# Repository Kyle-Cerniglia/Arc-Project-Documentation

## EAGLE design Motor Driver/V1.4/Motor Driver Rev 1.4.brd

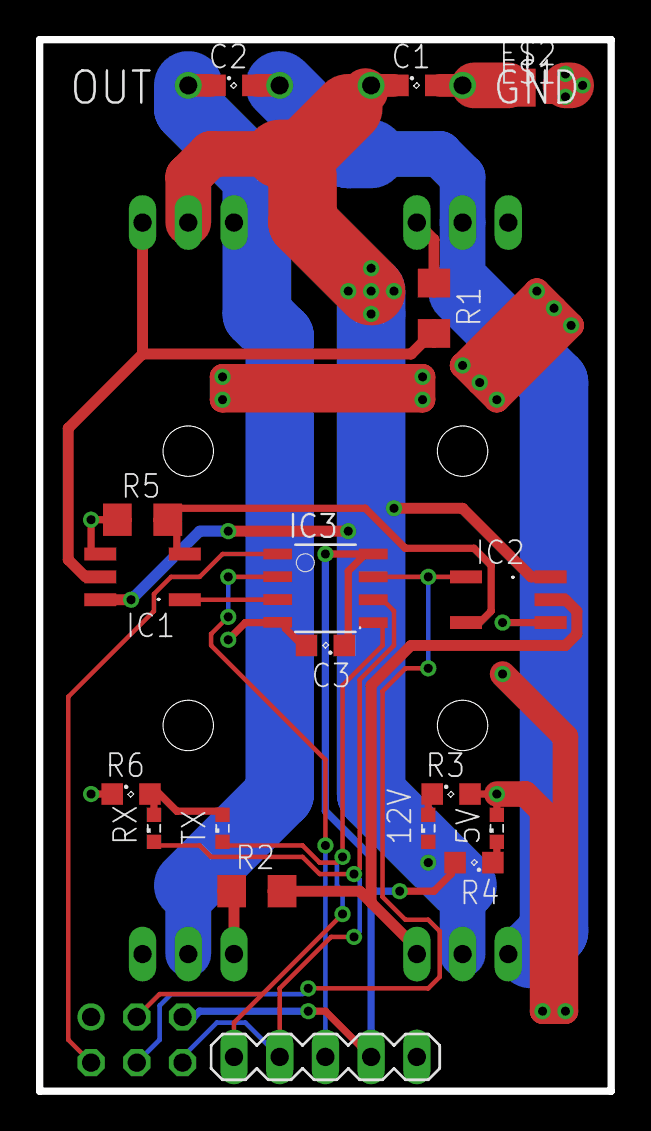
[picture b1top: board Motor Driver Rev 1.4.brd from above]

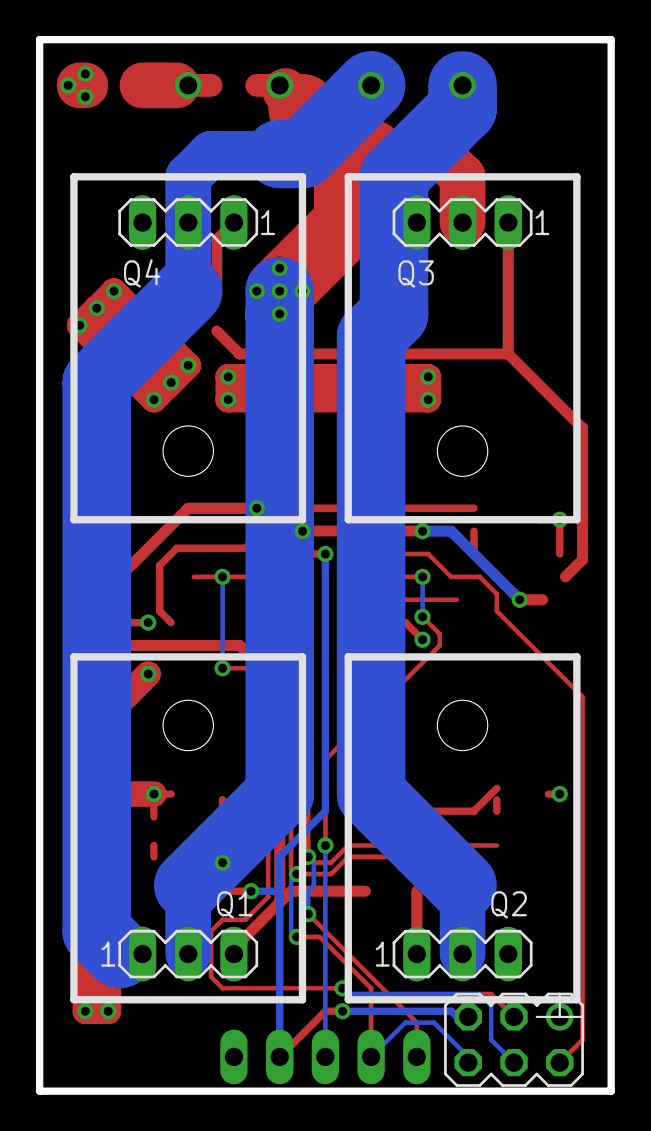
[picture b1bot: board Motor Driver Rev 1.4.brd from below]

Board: 2 copper layers, 31.8 x 58.4 mm, 24 parts (5 on the bottom side), 4 nets.

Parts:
5V, 12V: SML0603
C1, C2, C3: SML0805
E$1, E$2: POWERDI323
E$3: MA05-1
E$4: MA03-2
IC1, IC2: SOIC-6-5
IC3: 8S1
Q1, Q2, Q3, Q4: MA03-1
R1, R2, R5: PT1206
R3, R4, R6: SML0805
RX: SML0603
TX: SML0603

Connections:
GND: E$3.5, E$4.GND, Q2.GND, Q4.GND
S$28: E$3.2, E$4.6
S$33: E$3.4, E$4.5
S$37: E$3.GND, E$4.3

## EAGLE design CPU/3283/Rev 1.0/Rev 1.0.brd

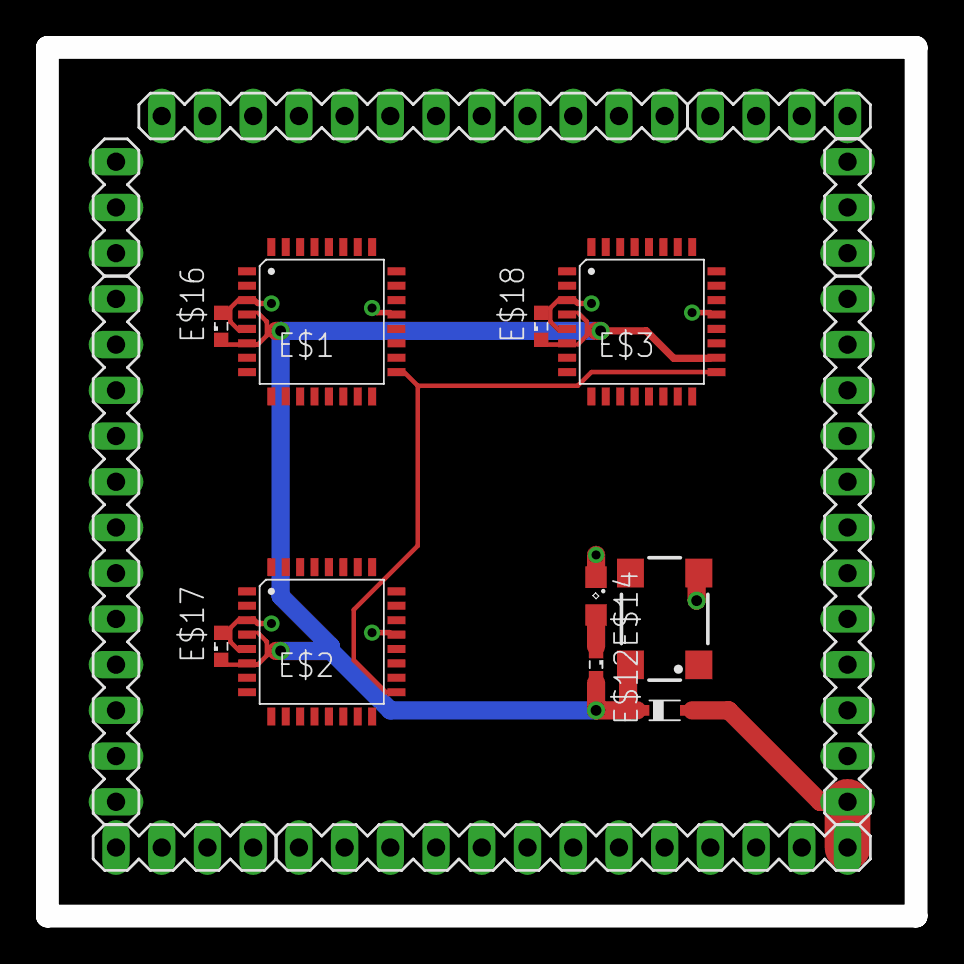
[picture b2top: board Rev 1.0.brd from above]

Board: 2 copper layers, 48.3 x 48.3 mm, 18 parts (0 on the bottom side), 2 nets.

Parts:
E$1, E$2, E$3: VQFP32
E$4: MA13-1
E$5, E$8: MA04-1
E$6, E$7, E$9: MA12-1
E$10, E$11: MA03-1
E$12, E$16, E$17, E$18: LED_SML0603
E$13: SM77H
E$14: SML0805
E$19: SOD323_ST

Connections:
GND: E$7.1, E$8.1
S$1: E$4.13, E$6.1

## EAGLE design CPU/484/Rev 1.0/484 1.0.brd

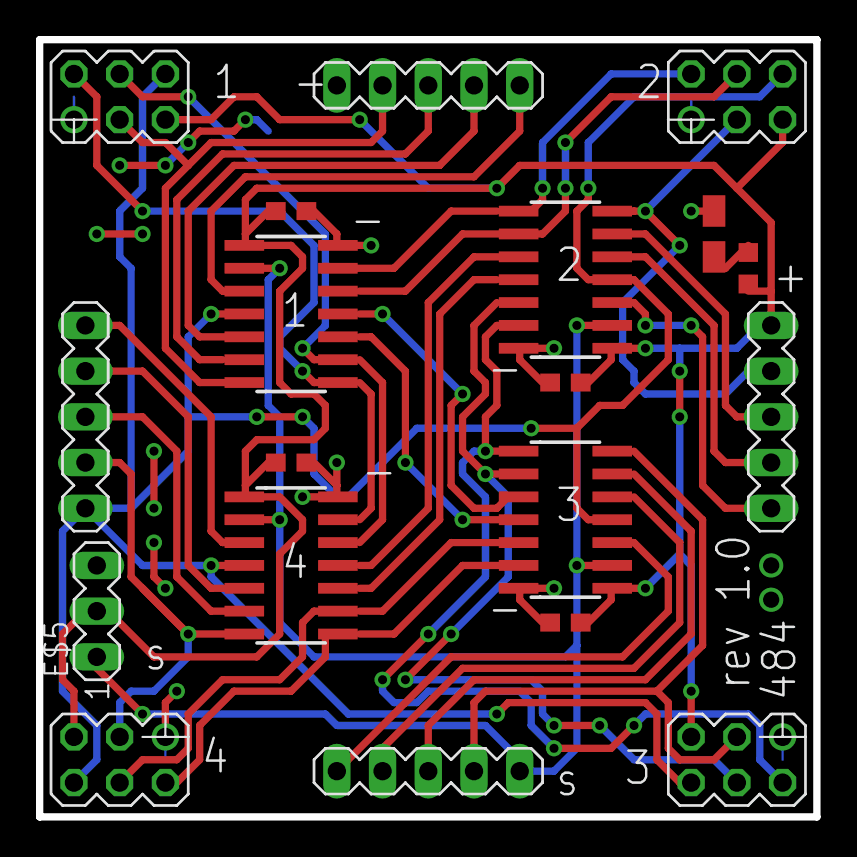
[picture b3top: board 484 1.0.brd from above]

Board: 2 copper layers, 43.2 x 43.2 mm, 19 parts (0 on the bottom side), 9 nets.

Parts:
E$1, E$2, E$3, E$4: SO14
E$5: MA03-1
E$6, E$8, E$9, E$20: MA05-1
E$10, E$11, E$12, E$13: C1608
E$14, E$15, E$16, E$17: MA03-2
E$18: C0603K
E$19: R/2012-12W

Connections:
GND: E$5.3, E$8.5, E$14.GND, E$15.GND, E$16.GND, E$17.GND
S$2: E$14.6, E$15.6, E$17.6, E$20.GND
S$8: E$5.2, E$14.5
S$15: E$14.3, E$20.2
S$21: E$9.GND, E$15.5, E$16.5, E$17.5
S$40: E$9.2, E$16.3
S$41: E$6.4, E$15.3
S$44: E$8.4, E$17.3
S$50: E$5.1, E$6.5

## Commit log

2017-04-01 Create f
2017-04-01 Create t
